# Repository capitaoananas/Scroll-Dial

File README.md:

# Scroll-Dial
A scroll dial using the AS5600 sensor and a small macropad for ajusting stuff like functionality

## Features

- Smooth and very accurate scrolling up to 0.08°
- AS5600 sensor
- Wireless
- Macropad for more functionality 
# BOM

| Part             | Quantity | Price  | Link                                                                                                                                                                                                                                                                                                                                                                                                                                                                                                                                                                                                                                                                           | Notes                  |
| ---------------- | -------- | ------ | ------------------------------------------------------------------------------------------------------------------------------------------------------------------------------------------------------------------------------------------------------------------------------------------------------------------------------------------------------------------------------------------------------------------------------------------------------------------------------------------------------------------------------------------------------------------------------------------------------------------------------------------------------------------------------ | ---------------------- |
| PCB              | 5        | $8.84  | [jlcpcb](https://jlcpcb.com/)                                                                                                                                                                                                                                                                                                                                                                                                                                                                                                                                                                                                                                                  |                        |
| Bearing          | 1        | $42.19 | [aliexpress](https://pt.aliexpress.com/item/1005007985984153.html?spm=a2g0o.productlist.main.39.177e4ab0I7Q0IH&algo_pvid=f89d27fe-3c35-48ed-8165-119fb4d5e36b&algo_exp_id=f89d27fe-3c35-48ed-8165-119fb4d5e36b-38&pdp_ext_f=%7B%22order%22%3A%225%22%2C%22eval%22%3A%221%22%2C%22fromPage%22%3A%22search%22%7D&pdp_npi=6%40dis%21EUR%2126.28%2124.95%21%21%2129.61%2128.11%21%40211b653717637426762538405e0fe2%2112000043164028783%21sea%21PT%210%21ABX%211%210%21n_tag%3A-29910%3Bd%3Ae275294c%3Bm03_new_user%3A-29895%3BpisId%3A5000000190669017&curPageLogUid=6ZjAFmZhltYG&utparam-url=scene%3Asearch%7Cquery_from%3A%7Cx_object_id%3A1005007985984153%7C_p_origin_prod%3A) |                        |
| Leds             | 100      | $4.51  | [aliexpress](https://pt.aliexpress.com/item/1005005186515165.html?spm=a2g0o.cart.0.0.705738daIoYdzj&mp=1&pdp_npi=5%40dis%21EUR%21EUR%203.89%21EUR%203.89%21%21EUR%203.89%21%21%21%40211b819117645104650325232e8b7d%2112000032026120161%21ct%21PT%216372042523%21%211%210&gatewayAdapt=glo2bra)                                                                                                                                                                                                                                                                                                                                                                                 |                        |
| 3v to 5V step up | 1        | $2.54  | [aliexpress](https://pt.aliexpress.com/item/1005008417702599.html?spm=a2g0o.cart.0.0.705738daIoYdzj&mp=1&pdp_npi=5%40dis%21EUR%21EUR%202.19%21EUR%202.19%21%21EUR%202.12%21%21%21%40211b819117645104650325232e8b7d%2112000044973129059%21ct%21PT%216372042523%21%211%210&gatewayAdapt=glo2bra)                                                                                                                                                                                                                                                                                                                                                                                 |                        |
| Battery          | 2        | $8.03  | [aliexpress](https://www.aliexpress.com/item/1005007590699841.html?spm=a2g0o.cart.0.0.705738daIoYdzj&mp=1&pdp_npi=5%40dis%21EUR%21EUR%2011.94%21EUR%206.93%21%21EUR%206.73%21%21%21%40211b819117645104650325232e8b7d%2112000041417088349%21ct%21PT%216372042523%21%211%210&pdp_ext_f=%7B%22cart2PdpParams%22%3A%7B%22pdpBusinessMode%22%3A%22retail%22%7D%7D)                                                                                                                                                                                                                                                                                                                  |                        |
| Keycaps          | 10       | $4.78  | [aliexpress](https://www.aliexpress.com/item/4000354001038.html?spm=a2g0o.cart.0.0.705738daIoYdzj&mp=1&pdp_npi=5%40dis%21EUR%21EUR%204.67%21EUR%204.12%21%21EUR%204.04%21%21%21%40211b819117645104650325232e8b7d%2112000033499031133%21ct%21PT%216372042523%21%211%210)                                                                                                                                                                                                                                                                                                                                                                                                        |                        |
| Power Switch     | 10       | $10.38 | [aliexpress](https://www.aliexpress.com/item/1005008771937227.html?spm=a2g0o.cart.0.0.705738daIoYdzj&mp=1&pdp_npi=5%40dis%21EUR%21EUR%208.95%21EUR%208.95%21%21EUR%208.95%21%21%21%40211b819117645104650325232e8b7d%2112000046606678311%21ct%21PT%216372042523%21%211%210)                                                                                                                                                                                                                                                                                                                                                                                                     |                        |
| Pin Header       | 10       | $1.28  | [aliexpress](https://www.aliexpress.com/item/1005005112381207.html?spm=a2g0o.cart.0.0.705738daIoYdzj&mp=1&pdp_npi=5%40dis%21EUR%21EUR%201.10%21EUR%201.10%21%21EUR%201.10%21%21%21%40211b819117645104650325232e8b7d%2112000031702599010%21ct%21PT%216372042523%21%211%210)                                                                                                                                                                                                                                                                                                                                                                                                     |                        |
| AS5600 board     | 1        | $1.31  | [aliexpress](https://pt.aliexpress.com/item/1005001621701959.html?spm=a2g0o.cart.0.0.591c38dawoiWqH&mp=1&pdp_npi=5%40dis!EUR!EUR%201.33!EUR%201.13!!EUR%201.13!!!%40211b819117652863738462826e425a!12000016846497264!ct!PT!6372042523!!1!0&gatewayAdapt=glo2bra)                                                                                                                                                                                                                                                                                                                                                                                                               | To desolder components |

**Total:** $83.86

# Overview

This will cover the PCB, Schematic and 3D models of both the Sccoll dial as the Macropad

---
## Schematic

The Schematic was made in KiCAD

|                       Dial                       |                       Macropad                       |
| :----------------------------------------------: | :--------------------------------------------------: |
|  |  |

---
## PCB

The PCB's was made in KiCAD

|                       Dial                       |                       Macropad                       |
| :----------------------------------------------: | :--------------------------------------------------: |
|  |  |

---
## 3D models

All the models were made in Fusion

### Dial

|                                         Base                                          |                                          Top                                           | Bottom                                                     |
| :-----------------------------------------------------------------------------------: | :------------------------------------------------------------------------------------: | ---------------------------------------------------------- |
|  |      |  |
|                                     Base with PCB                                     |                                      Fully built                                       | Bare PCB                                                   |
|  |  |  |

---

### Macropad

|                                             Top                                              |                                             Side                                             | ON/OFF and USBC                                                                             |
| :------------------------------------------------------------------------------------------: | :------------------------------------------------------------------------------------------: | ------------------------------------------------------------------------------------------- |
|  |  |  |

---

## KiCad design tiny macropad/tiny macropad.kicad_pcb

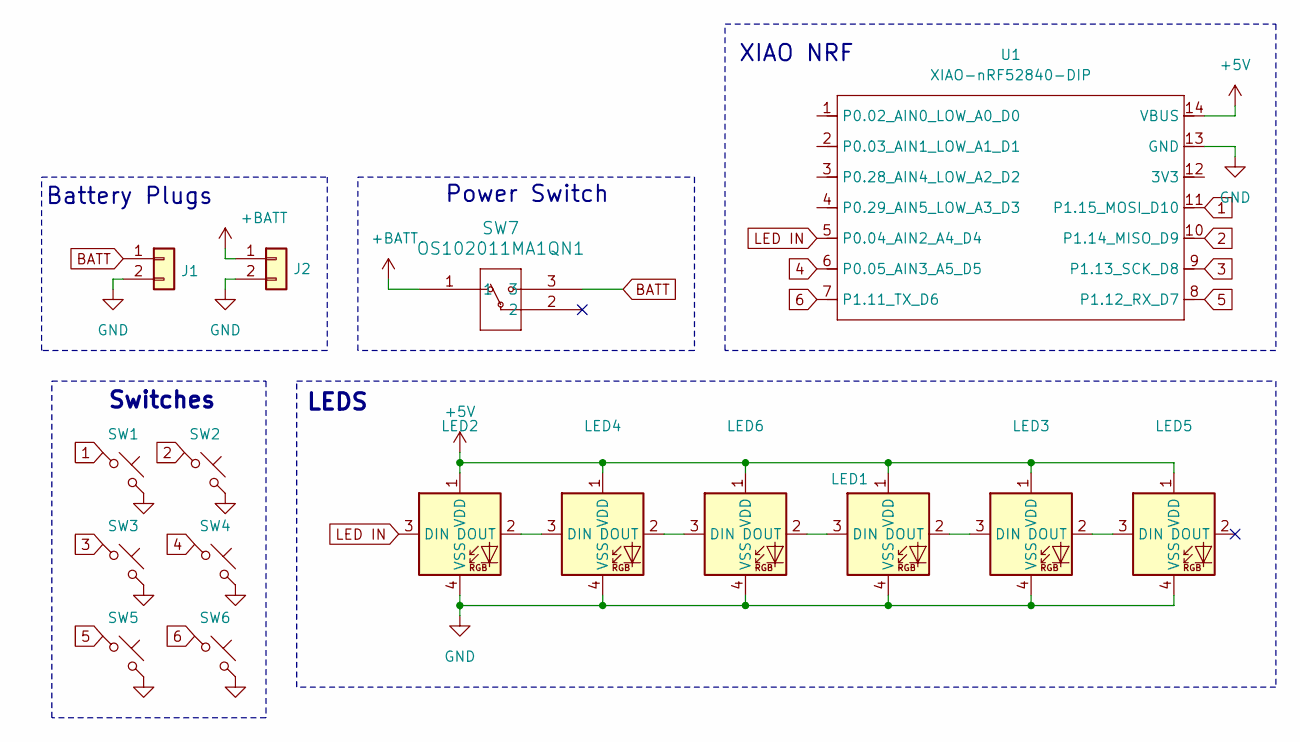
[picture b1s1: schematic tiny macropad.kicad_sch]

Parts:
J1, J2: Conn_01x02; PinHeader_1x02_P2.54mm_Vertical
LED1, LED2, LED3, LED4, LED5, LED6: MX_SK6812MINI-E; LED_6028R
SW1, SW2, SW3, SW4, SW5, SW6: SW_Push_45deg; MX-Solderable-1U
SW7: OS102011MA1QN1; OS102011MA1QN1_CNK
U1: XIAO-nRF52840-DIP

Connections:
1: SW1.1, U1.11 (P1.15_MOSI_D10)
2: SW2.1, U1.10 (P1.14_MISO_D9)
3: SW3.1, U1.9 (P1.13_SCK_D8)
4: SW4.1, U1.6 (P0.05_AIN3_A5_D5)
5: SW5.1, U1.8 (P1.12_RX_D7)
6: SW6.1, U1.7 (P1.11_TX_D6)
+5V: LED1.1 (VDD), LED2.1 (VDD), LED3.1 (VDD), LED4.1 (VDD), LED5.1 (VDD), LED6.1 (VDD), U1.14 (VBUS)
+BATT: J2.1, SW7.1
BATT: J1.1, SW7.3
GND: J1.2, J2.2, LED1.4 (VSS), LED2.4 (VSS), LED3.4 (VSS), LED4.4 (VSS), LED5.4 (VSS), LED6.4 (VSS), SW1.2, SW2.2, SW3.2, SW4.2, SW5.2, SW6.2, U1.13 (GND)
LED IN: LED2.3 (DIN), U1.5 (P0.04_AIN2_A4_D4)
unnamed: LED1.3 (DIN), LED6.2 (DOUT)
unnamed: LED1.2 (DOUT), LED3.3 (DIN)
unnamed: LED2.2 (DOUT), LED4.3 (DIN)
unnamed: LED3.2 (DOUT), LED5.3 (DIN)
unnamed: LED4.2 (DOUT), LED6.3 (DIN)

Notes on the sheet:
Battery Plugs
Power Switch
Switches
XIAO NRF
LEDS

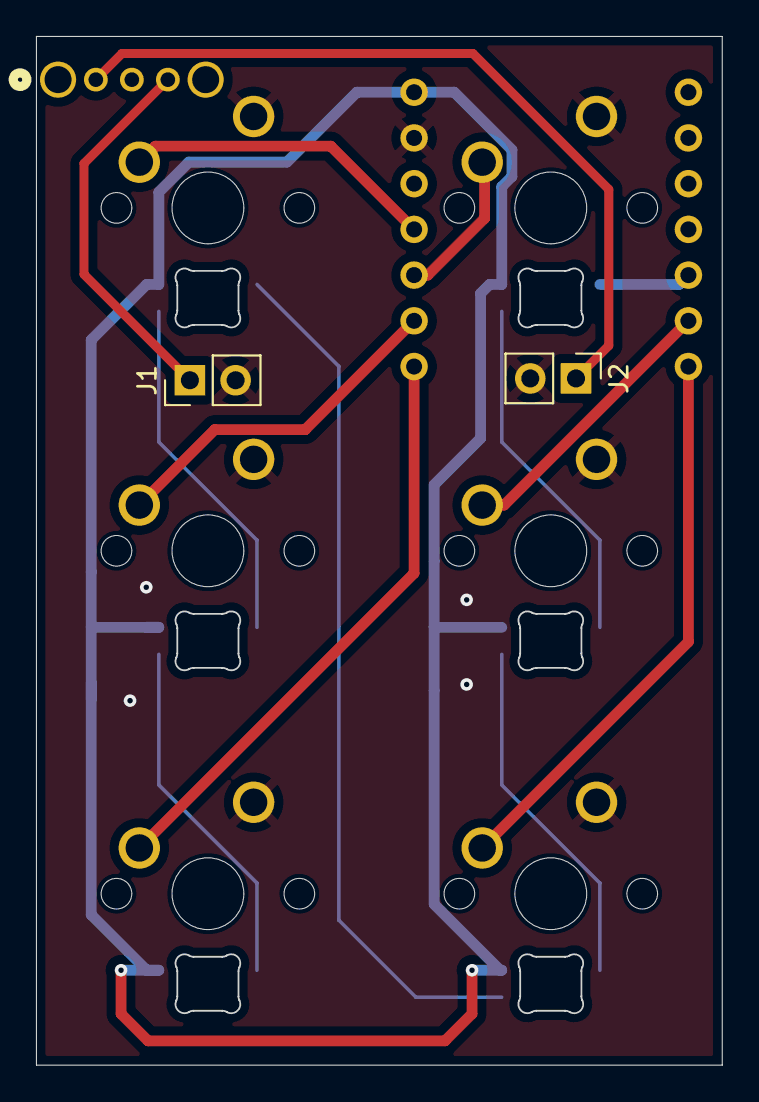
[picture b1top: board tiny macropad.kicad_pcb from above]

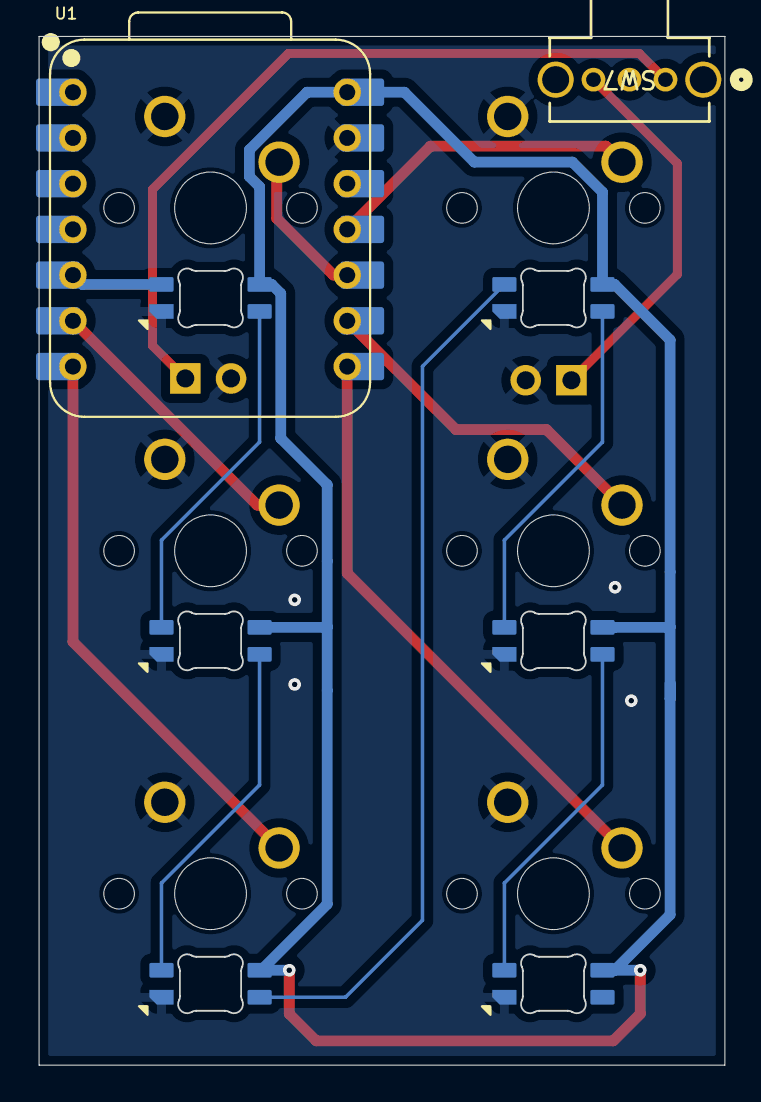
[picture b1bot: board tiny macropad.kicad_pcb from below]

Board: 2 copper layers, 38.0 x 57.1 mm, 16 parts (8 on the bottom side), 16 nets.

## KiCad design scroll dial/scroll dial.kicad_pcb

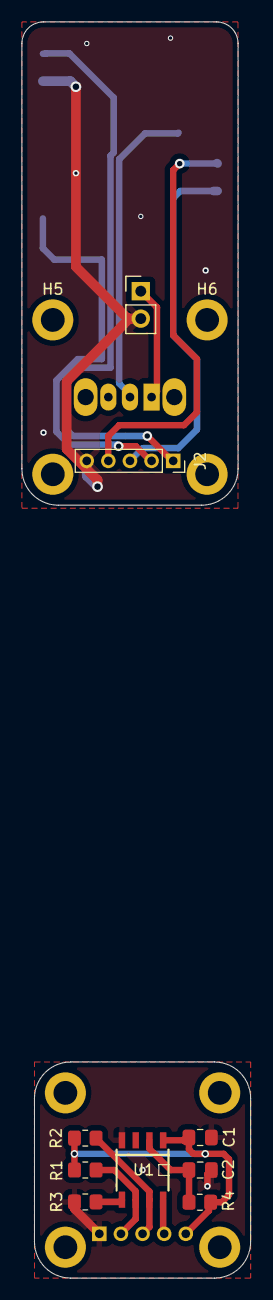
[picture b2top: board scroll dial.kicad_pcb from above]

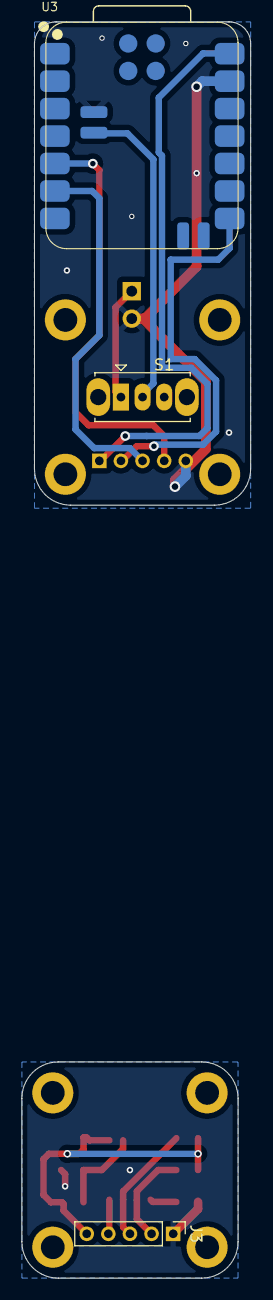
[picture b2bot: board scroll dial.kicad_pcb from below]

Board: 2 copper layers, 21.2 x 116.2 mm, 20 parts (3 on the bottom side), 9 nets.

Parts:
C1: 100 nF; C_0805_2012Metric_Pad1.18x1.45mm_HandSolder
C2: 6,7uF; C_0805_2012Metric_Pad1.18x1.45mm_HandSolder
H1, H2, H3, H4, H5, H6, H7, H8: MountingHole; MountingHole_2.2mm_M2_DIN965_Pad
J1: Conn_01x02_Pin; PinHeader_1x02_P2.54mm_Vertical
J2: Conn_01x05_Pin; PinSocket_1x05_P2.00mm_Vertical
J3: Conn_01x05_Pin; PinHeader_1x05_P2.00mm_Vertical
R1, R2: 10K; R_0805_2012Metric_Pad1.20x1.40mm_HandSolder
R3: 1k; R_0805_2012Metric_Pad1.20x1.40mm_HandSolder
R4: 0; R_0805_2012Metric_Pad1.20x1.40mm_HandSolder
S1: OS102011MS2QN1; SW_Slide_SPDT_Straight_CK_OS102011MS2Q
U1: AS5600; SOIC8
U3: XIAO-nRF52840-SMD

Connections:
+BATT: S1.2, U3.15 (BAT)
Battery terminal +: J1.1, S1.1
DIR: J2.2, J3.4, U1.8 (DIR), U3.8 (P1.12_D7_RX)
GND: C1.2, C2.2, J1.2, J2.5, J3.1, R3.2, U1.4 (GND), U3.13 (GND), U3.16 (GND)
PGO: R3.1, U1.5 (PGO)
SCL: J2.3, J3.3, R2.2, U1.7 (SCL), U3.6 (P0.05_A5_D5_SCL)
SDA: J2.4, J3.2, R1.2, U1.6 (SDA), U3.5 (P0.04_A4_D4_SDA)
VCC: C1.1, J2.1, J3.5, R1.1, R2.1, R4.1, U1.1 (VDD5V), U3.14 (5V)
VDD3V3: C2.1, R4.2, U1.2 (VDD3V3)

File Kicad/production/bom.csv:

Designator,Footprint,Quantity,Value,LCSC Part #
C1,0805,1,100 nF,
C2,0805,1,"6,7uF",
J1_2,PinHeader_1x02_P2.54mm_Vertical,1,Conn_01x02_Pin,
"J1, J2",PinHeader_1x02_P2.54mm_Vertical,2,Conn_01x02,
"J2_2, J3",PinHeader_1x05_P2.00mm_Vertical,2,Conn_01x05_Pin,
"LED1, LED2, LED3, LED4, LED5, LED6",LED_6028R,6,MX_SK6812MINI-E,
"R1, R2",0805,2,10K,
R3,0805,1,1k,
R4,0805,1,0,
"SW1_2, SW2, SW3, SW4, SW5, SW6",MX-Solderable-1U,6,SW_Push_45deg,
"SW1, SW7",OS102011MA1QN1_CNK,2,OS102011MA1QN1,
U1_2,SOIC8,1,AS5600,
U1,XIAO-nRF52840-DIP,1,XIAO-nRF52840-DIP,
U3,XIAO-nRF52840-SMD,1,XIAO-nRF52840-SMD,

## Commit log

2025-11-20 add pcb step files
2025-11-30 Update product prices and links in README
2025-12-01 test
2025-12-02 add photos to README
2025-12-02 add 3D
2025-12-02 fix a bit in README
2025-12-09 add firmware
2025-12-09 update bom
2025-12-10 add production files
